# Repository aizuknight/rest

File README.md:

# rest
**rest** is a wired split keyboard which has 38 keys in total.

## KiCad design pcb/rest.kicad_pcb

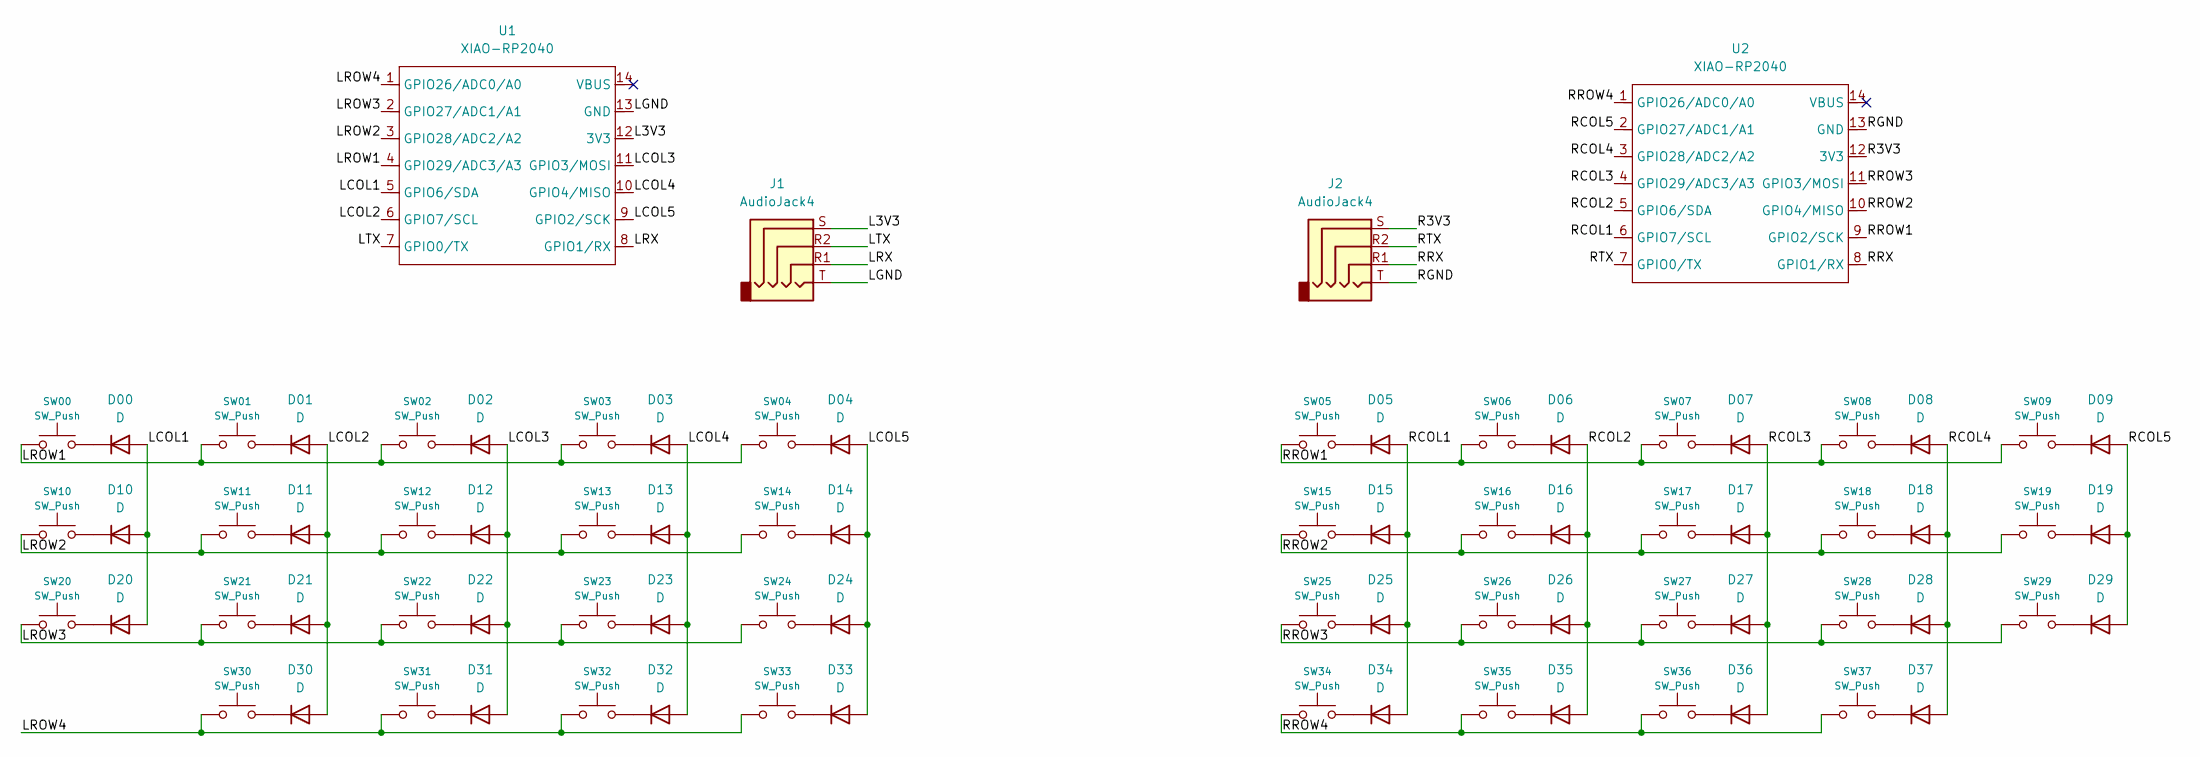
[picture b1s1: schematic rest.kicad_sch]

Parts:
D00, D01, D02, D03, D04, D05, D06, D07, D08, D09, D10, D11, D12, D13, D14, D15, D16, D17, D18, D19, D20, D21, D22, D23, D24, D25, D26, D27, D28, D29, D30, D31, D32, D33, D34, D35, D36, D37: D; 1N4148W
J1, J2: AudioJack4; MJ-4PP-9
SW00, SW01, SW02, SW03, SW04, SW05, SW06, SW07, SW08, SW09, SW10, SW11, SW12, SW13, SW14, SW15, SW16, SW17, SW18, SW19, SW20, SW21, SW22, SW23, SW24, SW25, SW26, SW27, SW28, SW29, SW30, SW31, SW33, SW34, SW36, SW37: SW_Push; keyswitch_cherrymx_hotswap_1u
SW32, SW35: SW_Push; keyswitch_cherrymx_hotswap_1.5u
U1, U2: XIAO-RP2040

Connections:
/L3V3: J1.S, U1.12 (3V3)
/LCOL1: D00.2 (A), D10.2 (A), D20.2 (A), U1.5 (GPIO6/SDA)
/LCOL2: D01.2 (A), D11.2 (A), D21.2 (A), D30.2 (A), U1.6 (GPIO7/SCL)
/LCOL3: D02.2 (A), D12.2 (A), D22.2 (A), D31.2 (A), U1.11 (GPIO3/MOSI)
/LCOL4: D03.2 (A), D13.2 (A), D23.2 (A), D32.2 (A), U1.10 (GPIO4/MISO)
/LCOL5: D04.2 (A), D14.2 (A), D24.2 (A), D33.2 (A), U1.9 (GPIO2/SCK)
/LGND: J1.T, U1.13 (GND)
/LROW1: SW00.1, SW01.1, SW02.1, SW03.1, SW04.1, U1.4 (GPIO29/ADC3/A3)
/LROW2: SW10.1, SW11.1, SW12.1, SW13.1, SW14.1, U1.3 (GPIO28/ADC2/A2)
/LROW3: SW20.1, SW21.1, SW22.1, SW23.1, SW24.1, U1.2 (GPIO27/ADC1/A1)
/LROW4: SW30.1, SW31.1, SW32.1, SW33.1, U1.1 (GPIO26/ADC0/A0)
/LRX: J1.R1, U1.8 (GPIO1/RX)
/LTX: J1.R2, U1.7 (GPIO0/TX)
/R3V3: J2.S, U2.12 (3V3)
/RCOL1: D05.2 (A), D15.2 (A), D25.2 (A), D34.2 (A), U2.6 (GPIO7/SCL)
/RCOL2: D06.2 (A), D16.2 (A), D26.2 (A), D35.2 (A), U2.5 (GPIO6/SDA)
/RCOL3: D07.2 (A), D17.2 (A), D27.2 (A), D36.2 (A), U2.4 (GPIO29/ADC3/A3)
/RCOL4: D08.2 (A), D18.2 (A), D28.2 (A), D37.2 (A), U2.3 (GPIO28/ADC2/A2)
/RCOL5: D09.2 (A), D19.2 (A), D29.2 (A), U2.2 (GPIO27/ADC1/A1)
/RGND: J2.T, U2.13 (GND)
/RROW1: SW05.1, SW06.1, SW07.1, SW08.1, SW09.1, U2.9 (GPIO2/SCK)
/RROW2: SW15.1, SW16.1, SW17.1, SW18.1, SW19.1, U2.10 (GPIO4/MISO)
/RROW3: SW25.1, SW26.1, SW27.1, SW28.1, SW29.1, U2.11 (GPIO3/MOSI)
/RROW4: SW34.1, SW35.1, SW36.1, SW37.1, U2.1 (GPIO26/ADC0/A0)
/RRX: J2.R1, U2.8 (GPIO1/RX)
/RTX: J2.R2, U2.7 (GPIO0/TX)
unnamed: D00.1 (K), SW00.2
unnamed: D01.1 (K), SW01.2
unnamed: D02.1 (K), SW02.2
unnamed: D03.1 (K), SW03.2
unnamed: D04.1 (K), SW04.2
unnamed: D05.1 (K), SW05.2
unnamed: D06.1 (K), SW06.2
unnamed: D07.1 (K), SW07.2
unnamed: D08.1 (K), SW08.2
unnamed: D09.1 (K), SW09.2
unnamed: D10.1 (K), SW10.2
unnamed: D11.1 (K), SW11.2
unnamed: D12.1 (K), SW12.2
unnamed: D13.1 (K), SW13.2
unnamed: D14.1 (K), SW14.2
unnamed: D15.1 (K), SW15.2
unnamed: D16.1 (K), SW16.2
unnamed: D17.1 (K), SW17.2
unnamed: D18.1 (K), SW18.2
unnamed: D19.1 (K), SW19.2
unnamed: D20.1 (K), SW20.2
unnamed: D21.1 (K), SW21.2
unnamed: D22.1 (K), SW22.2
unnamed: D23.1 (K), SW23.2
unnamed: D24.1 (K), SW24.2
unnamed: D25.1 (K), SW25.2
unnamed: D26.1 (K), SW26.2
unnamed: D27.1 (K), SW27.2
unnamed: D28.1 (K), SW28.2
unnamed: D29.1 (K), SW29.2
unnamed: D30.1 (K), SW30.2
unnamed: D31.1 (K), SW31.2
unnamed: D32.1 (K), SW32.2
unnamed: D33.1 (K), SW33.2
unnamed: D34.1 (K), SW34.2
unnamed: D35.1 (K), SW35.2
unnamed: D36.1 (K), SW36.2
unnamed: D37.1 (K), SW37.2

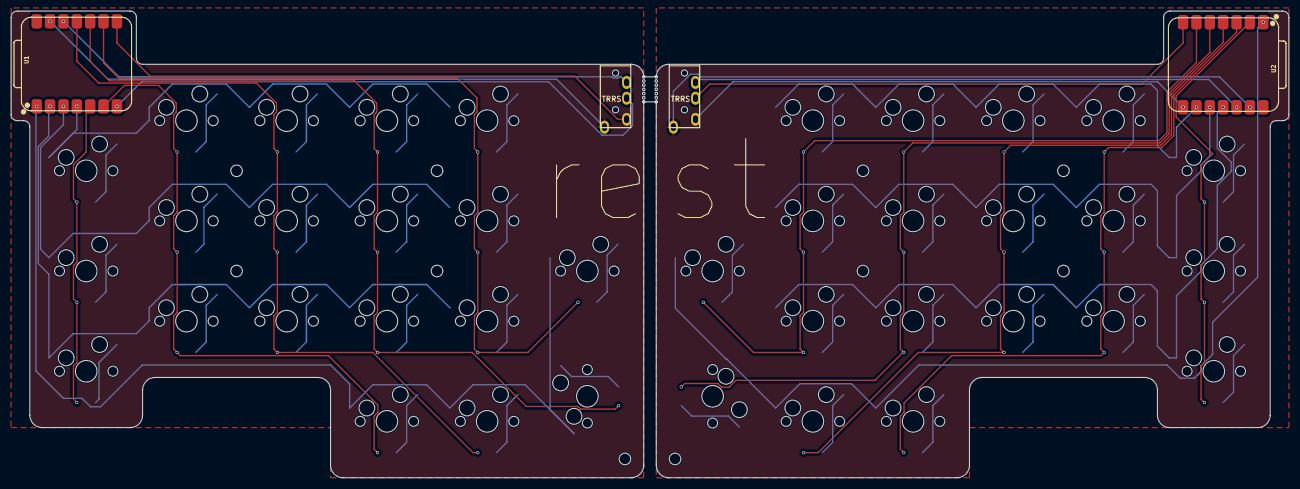
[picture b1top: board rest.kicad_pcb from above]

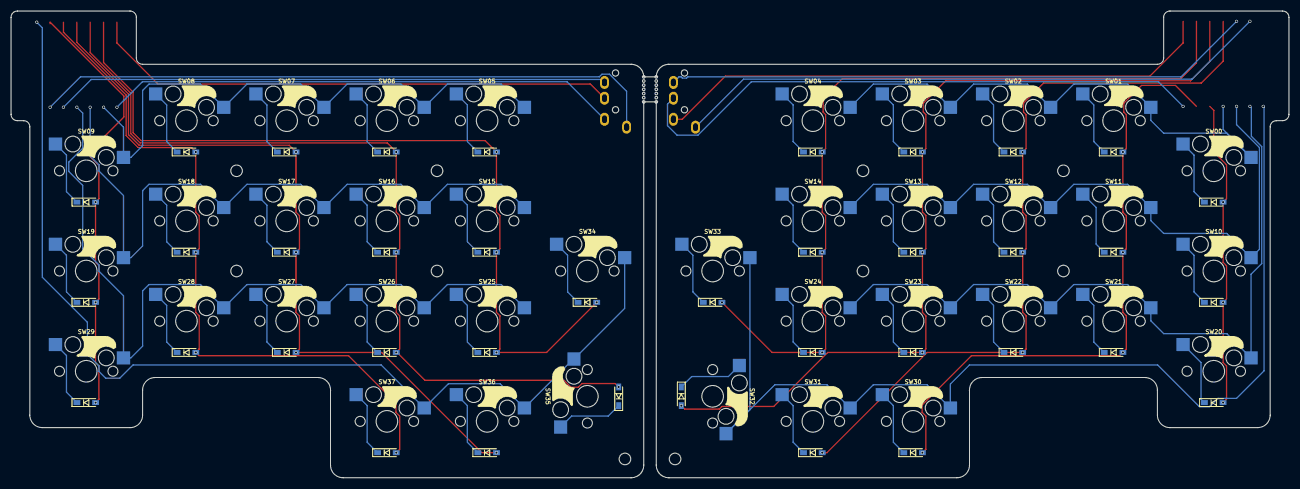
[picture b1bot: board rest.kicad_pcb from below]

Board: 2 copper layers, 242.9 x 88.7 mm, 80 parts (76 on the bottom side), 64 nets.

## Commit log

2026-04-20 Add image to README.md
2026-04-20 Add pcb design files
2026-04-20 Rename pcb design files
2026-06-03 Add firmware source code and build script
